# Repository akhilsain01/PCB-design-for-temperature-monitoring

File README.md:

"# PCB-design-for-temperature-monitoring"

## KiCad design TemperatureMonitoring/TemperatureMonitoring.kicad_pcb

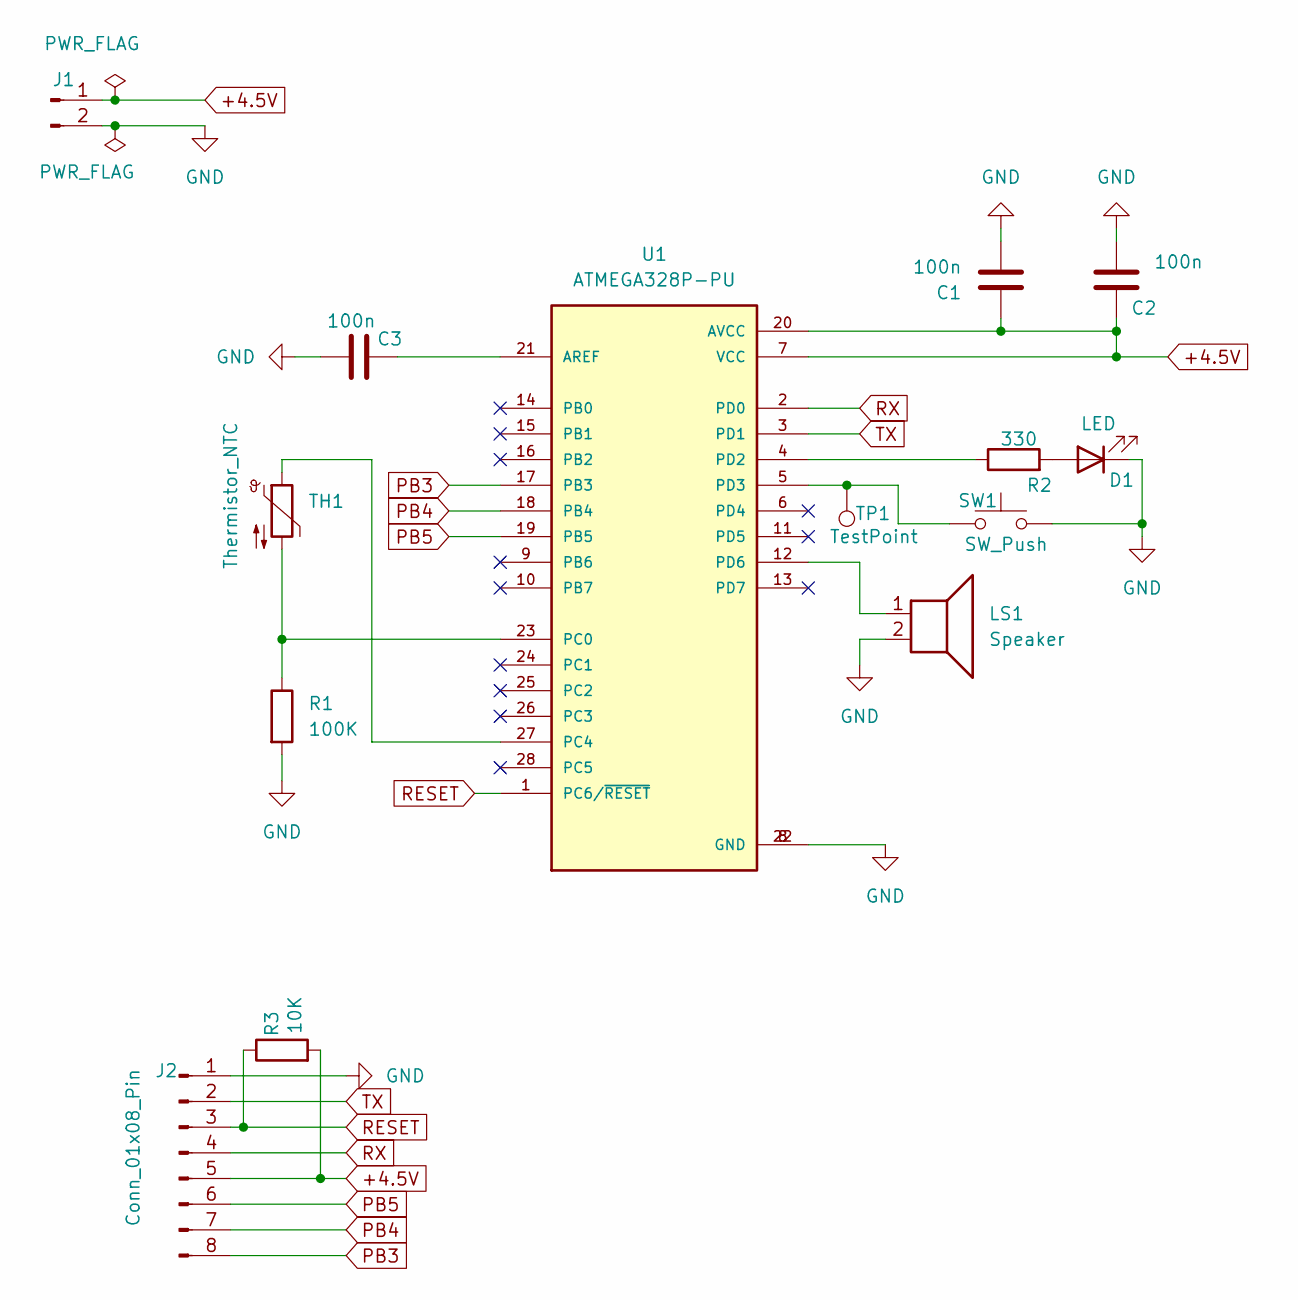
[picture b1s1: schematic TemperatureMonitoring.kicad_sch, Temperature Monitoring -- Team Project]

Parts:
C1, C2, C3: 100n; C_Disc_D5.0mm_W2.5mm_P2.50mm
D1: LED; LED_D5.0mm
J1: Conn_01x02_Pin; PinHeader_1x02_P2.54mm_Vertical
J2: Conn_01x08_Pin; PinHeader_1x08_P2.54mm_Vertical
LS1: Speaker; Buzzer_15x7.5RM7.6
R1: 100K; R_Axial_DIN0207_L6.3mm_D2.5mm_P10.16mm_Horizontal
R2: 330; R_Axial_DIN0207_L6.3mm_D2.5mm_P10.16mm_Horizontal
R3: 10K; R_Axial_DIN0207_L6.3mm_D2.5mm_P10.16mm_Horizontal
SW1: SW_Push; SW_PUSH_6mm_H7.3mm
TH1: Thermistor_NTC; R_Axial_DIN0207_L6.3mm_D2.5mm_P10.16mm_Horizontal
TP1: TestPoint; PinHeader_1x01_P2.54mm_Vertical
U1: ATMEGA328P-PU; DIP787W46P254L3467H508Q28

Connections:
+4.5V: C1.1, C2.1, J1.1, J2.5, R3.2, U1.7 (VCC), U1.20 (AVCC)
GND: C1.2, C2.2, C3.1, D1.1 (K), J1.2, J2.1, LS1.2, R1.2, SW1.2, U1.8 (GND), U1.22 (GND)
unnamed: D1.2 (A), R2.2
unnamed: C3.2, U1.21 (AREF)
unnamed: R1.1, TH1.2, U1.23 (PC0)
unnamed: TH1.1, U1.27 (PC4)
unnamed: R2.1, U1.4 (PD2)
unnamed: SW1.1, TP1.1, U1.5 (PD3)
unnamed: LS1.1, U1.12 (PD6)
PB3: J2.8, U1.17 (PB3)
PB4: J2.7, U1.18 (PB4)
PB5: J2.6, U1.19 (PB5)
RESET: J2.3, R3.1, U1.1 (PC6/~RESET)
RX: J2.4, U1.2 (PD0)
TX: J2.2, U1.3 (PD1)

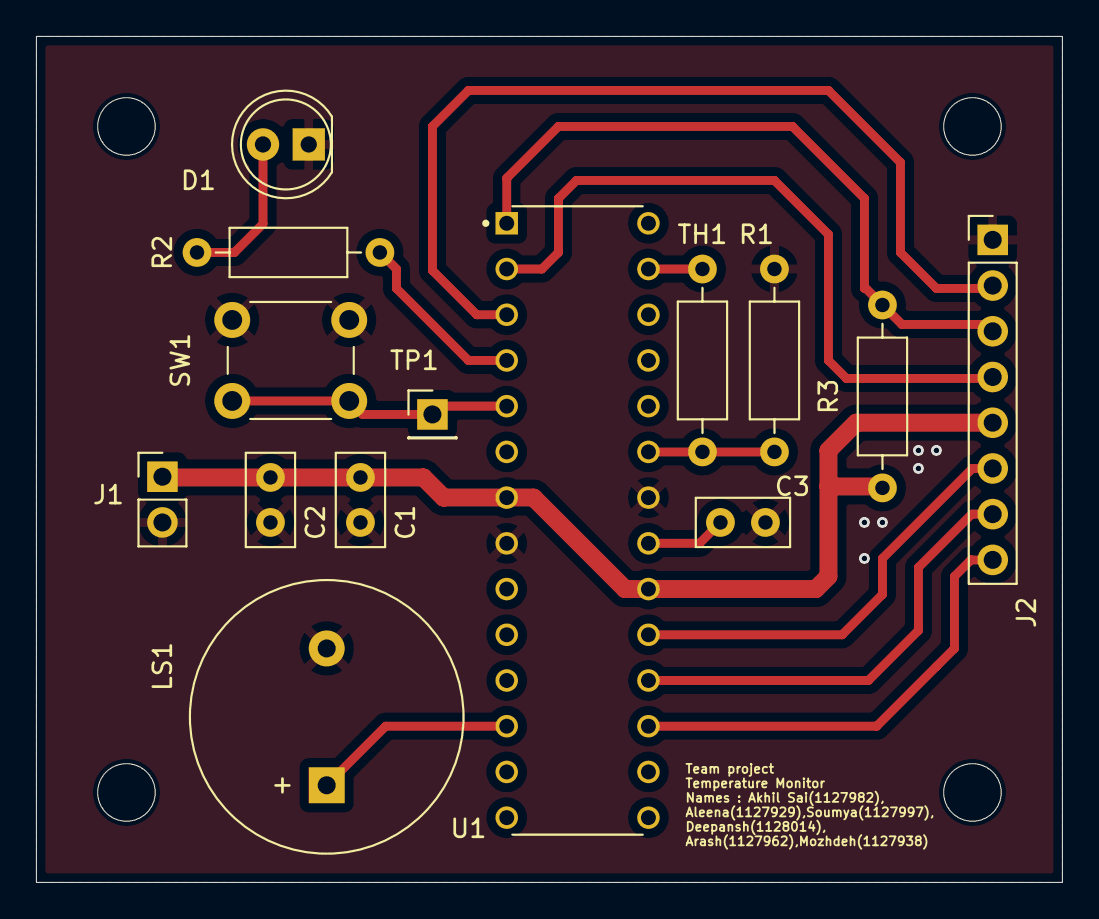
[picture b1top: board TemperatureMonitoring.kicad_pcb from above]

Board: 2 copper layers, 57.0 x 47.0 mm, 14 parts (0 on the bottom side), 15 nets.

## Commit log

2025-02-22 final PCB in 3D view from top
2025-02-26 mod hardware
